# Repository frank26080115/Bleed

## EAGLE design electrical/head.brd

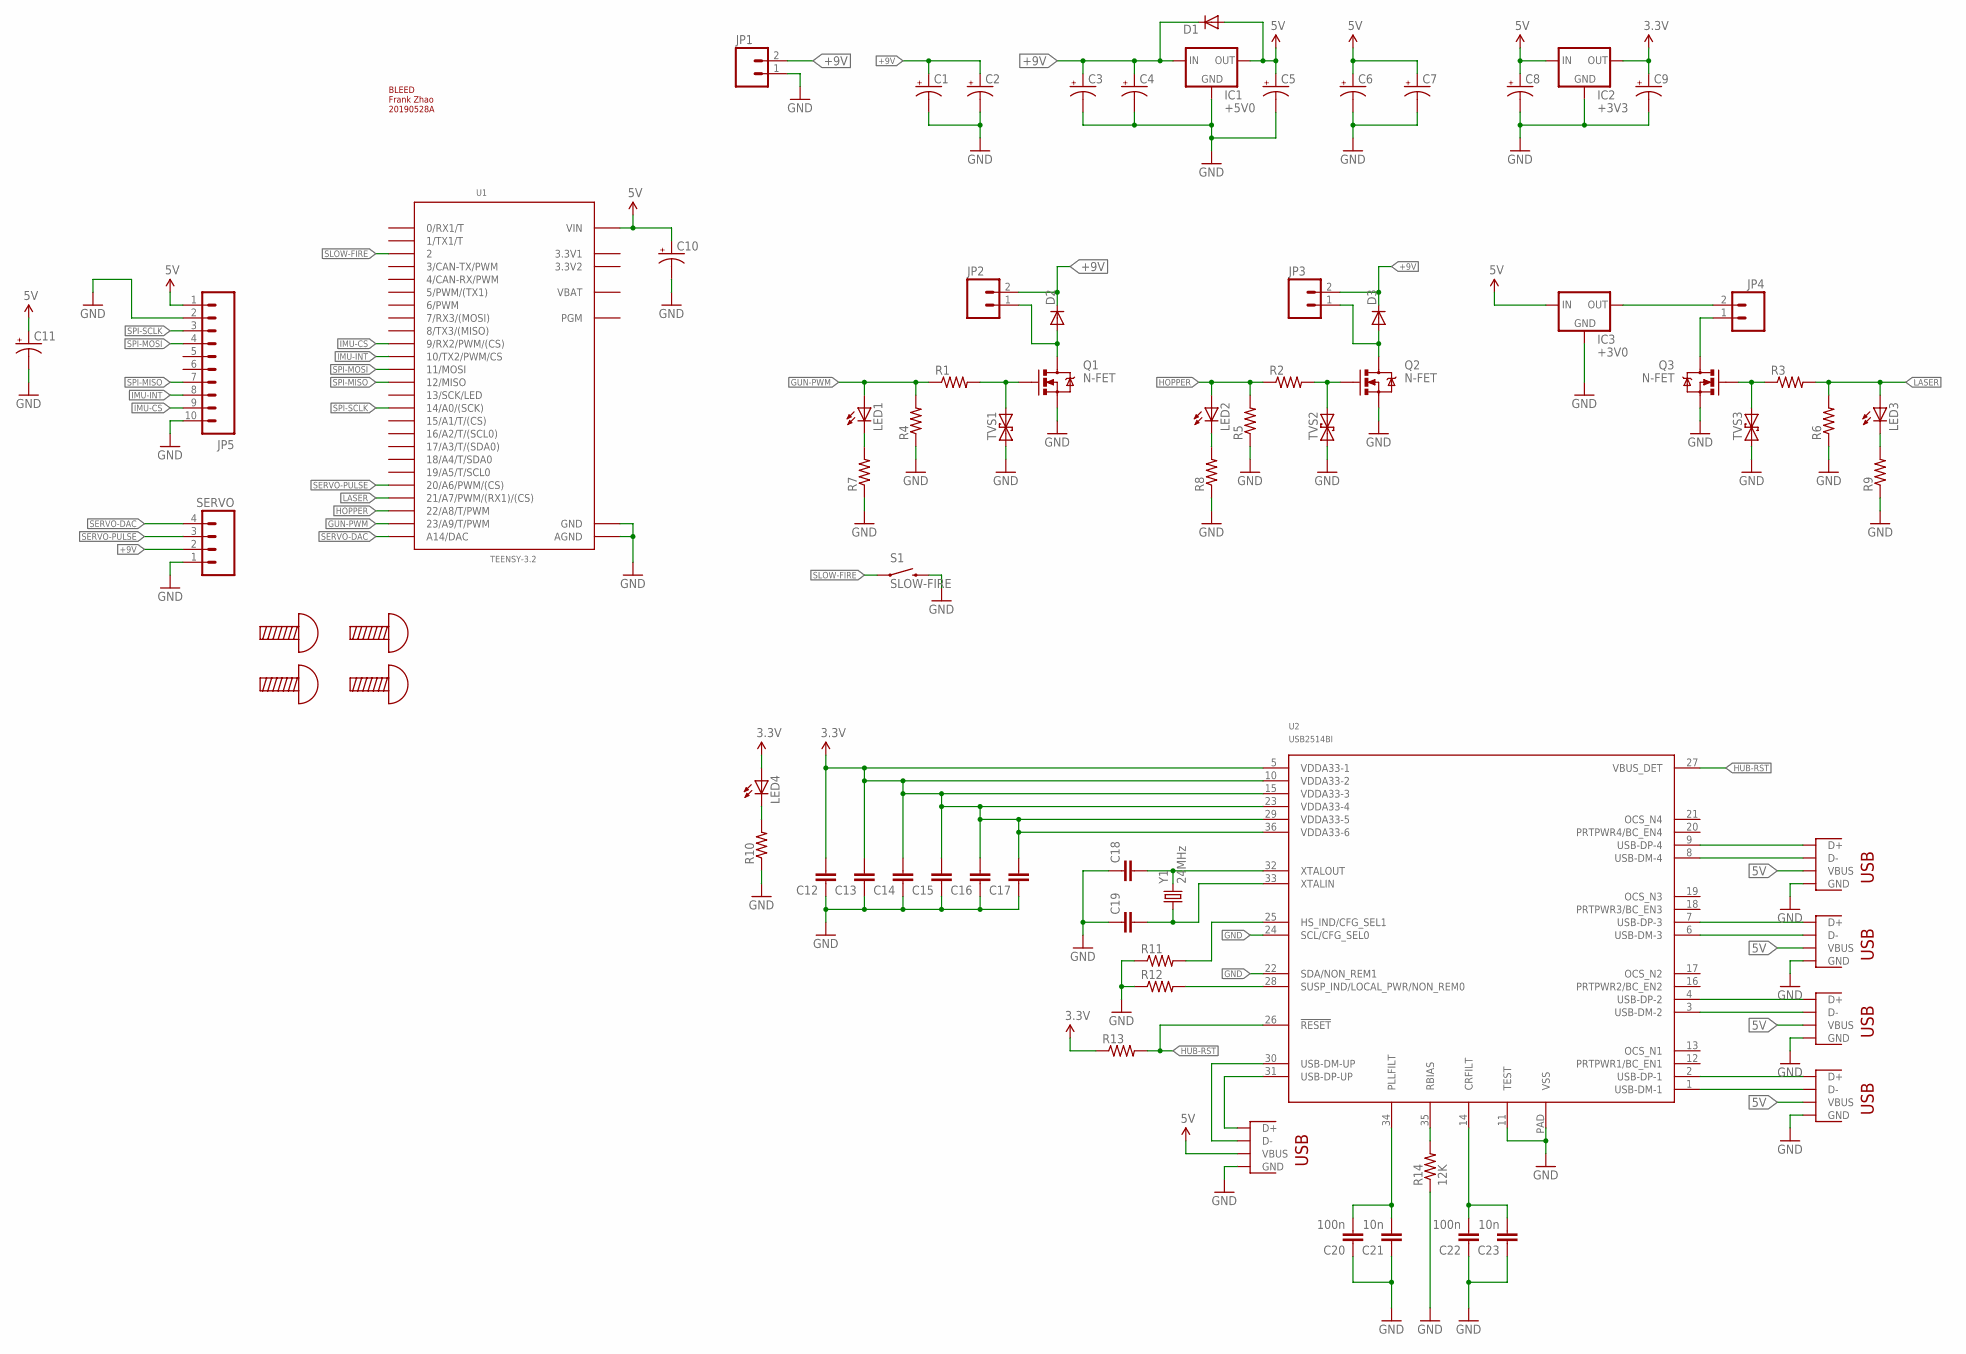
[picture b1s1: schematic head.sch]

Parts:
C1, C2, C3: CAP_POLPTH4; CPOL-RADIAL-1000UF-25V
C4, C5, C6, C7, C8, C9, C10, C11: CAP_POL1206-KIT; EIA3216-KIT
C12, C13, C14, C15, C16, C17, C18, C19: CAP0402-CAP; 0402-CAP
C20, C22: 100n; 0402-CAP
C21, C23: 10n; 0402-CAP
D1, D2, D3: DIODESMA-KIT; SMA-DIODE-KIT
IC1: +5V0; TO220V
IC2: +3V3; SOT23
IC3: +3V0; SOT23
JP1, JP2: M02-TERMBLOCK-3.5MM-OSTTF020161; TERMBLOCK-X2-OSTTF020161
JP3: M02POLAR; MOLEX-1X2
JP4: M02JST-PTH-2; JST-2-PTH
JP5: M10"; 1X10
LED1, LED2, LED3, LED4: LED0603; LED-0603
LOGO1: LOGO_BLEED
Q1, Q2: N-FET; TO220V
Q3: N-FET; SOT23-3
R1, R2, R3, R4, R5, R6, R7, R8, R9: RESISTOR0603-RES; 0603-RES
R10, R11, R12, R13: RESISTOR0402-RES; 0402-RES
R14: 12K; 0402-RES
S1: SLOW-FIRE; TACTILE-SWITCH-1101NE
SCREW1, SCREW2, SCREW3, SCREW4: SCREW-M3
SERVO: M04POLAR; MOLEX-1X4
TVS1, TVS2, TVS3: TVS-SOD323; SOD-323
U1: TEENSY-3.2; TEENSY_3.0-3.2&LC_OUTER_ROW
U2: USB2514BI; QFN-36
X1, X2, X3, X4, X5: USB-JSTXH-VERT-TH; 1X04-JSTXH-VERT-TH
Y1: 24MHz; CRYSTAL-SMD-5X3

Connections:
3.3V: C9.A (+), C12.2, C13.2, C14.2, C15.2, C16.2, C17.2, IC2.2 (OUT), LED4.A, R13.1, U2.5 (VDDA33-1), U2.10 (VDDA33-2), U2.15 (VDDA33-3), U2.23 (VDDA33-4), U2.29 (VDDA33-5), U2.36 (VDDA33-6)
3.3V1: U1.3.3V1
3.3V2: U1.3.3V2
5V: C5.A (+), C6.A (+), C7.A (+), C8.A (+), C10.A (+), C11.A (+), D1.A, IC1.3 (OUT), IC2.3 (IN), IC3.3 (IN), JP5.1, U1.VIN, X1.1 (VBUS), X2.1 (VBUS), X3.1 (VBUS), X4.1 (VBUS), X5.1 (VBUS)
+9V: C1.1 (+), C2.1 (+), C3.1 (+), C4.A (+), D1.C, D2.C, D3.C, IC1.1 (IN), JP1.2, JP2.2, JP3.2, SERVO.2
GND: C1.2 (-), C2.2 (-), C3.2 (-), C4.C (-), C5.C (-), C6.C (-), C7.C (-), C8.C (-), C9.C (-), C10.C (-), C11.C (-), C12.1, C13.1, C14.1, C15.1, C16.1, C17.1, C18.1, C19.1, C20.1, C21.1, C22.1, C23.1, IC1.2 (GND), IC2.1 (GND), IC3.1 (GND), JP1.1, JP5.2, JP5.10, Q1.3 (S), Q2.3 (S), Q3.2 (S), R4.1, R5.1, R6.1, R7.1, R8.1, R9.1, R10.1, R11.1, R12.1, R14.1, S1.2, SERVO.1, TVS1.1, TVS2.1, TVS3.1, U1.AGND, U1.GND, U1.GND1 (GND), U2.11 (TEST), U2.22 (SDA/NON_REM1), U2.24 (SCL/CFG_SEL0), U2.PAD (VSS), X1.4 (GND), X2.4 (GND), X3.4 (GND), X4.4 (GND), X5.4 (GND)
GUN-PWM: LED1.A, R1.1, R4.2, U1.23/A9 (23/A9/T/PWM)
HOPPER: LED2.A, R2.1, R5.2, U1.22/A8 (22/A8/T/PWM)
HUB-RST: R13.2, U2.26 (!RESET), U2.27 (VBUS_DET)
IMU-CS: JP5.9, U1.9 (9/RX2/PWM/(CS))
IMU-INT: JP5.8, U1.10 (10/TX2/PWM/CS)
LASER: LED3.A, R3.2, R6.2, U1.21/A7 (21/A7/PWM/(RX1)/(CS))
unnamed: C18.2, U2.32 (XTALOUT), Y1.3 (2)
unnamed: D2.A, JP2.1, Q1.2 (D)
unnamed: LED4.C, R10.2
unnamed: Q1.1 (G), R1.2, TVS1.2
unnamed: C19.2, U2.33 (XTALIN), Y1.1
unnamed: C20.2, C21.2, U2.34 (PLLFILT)
unnamed: D3.A, JP3.1, Q2.2 (D)
unnamed: Q2.1 (G), R2.2, TVS2.2
unnamed: JP4.1, Q3.3 (D)
unnamed: IC3.2 (OUT), JP4.2
unnamed: LED1.C, R7.2
unnamed: Q3.1 (G), R3.1, TVS3.2
unnamed: LED2.C, R8.2
unnamed: C22.2, C23.2, U2.14 (CRFILT)
unnamed: LED3.C, R9.2
unnamed: R14.2, U2.35 (RBIAS)
unnamed: R11.2, U2.25 (HS_IND/CFG_SEL1)
unnamed: R12.2, U2.28 (SUSP_IND/LOCAL_PWR/NON_REM0)
SERVO-DAC: SERVO.4, U1.RESET/DAC (A14/DAC)
SERVO-PULSE: SERVO.3, U1.20/A6 (20/A6/PWM/(CS))
SLOW-FIRE: S1.1, U1.2
SPI-MISO: JP5.7, U1.12 (12/MISO)
SPI-MOSI: JP5.4, U1.11 (11/MOSI)
SPI-SCLK: JP5.3, U1.14/A0 (14/A0/(SCK))
USB_DOWN1_D_N: U2.1 (USB-DM-1), X4.3 (D-)
USB_DOWN1_D_P: U2.2 (USB-DP-1), X4.2 (D+)
USB_DOWN2_D_N: U2.3 (USB-DM-2), X3.3 (D-)
USB_DOWN2_D_P: U2.4 (USB-DP-2), X3.2 (D+)
USB_DOWN3_D_N: U2.6 (USB-DM-3), X2.3 (D-)
USB_DOWN3_D_P: U2.7 (USB-DP-3), X2.2 (D+)
USB_DOWN4_D_N: U2.8 (USB-DM-4), X1.3 (D-)
USB_DOWN4_D_P: U2.9 (USB-DP-4), X1.2 (D+)
USB_UP_D_N: U2.31 (USB-DP-UP), X5.2 (D+)
USB_UP_D_P: U2.30 (USB-DM-UP), X5.3 (D-)
VBAT: U1.VBAT

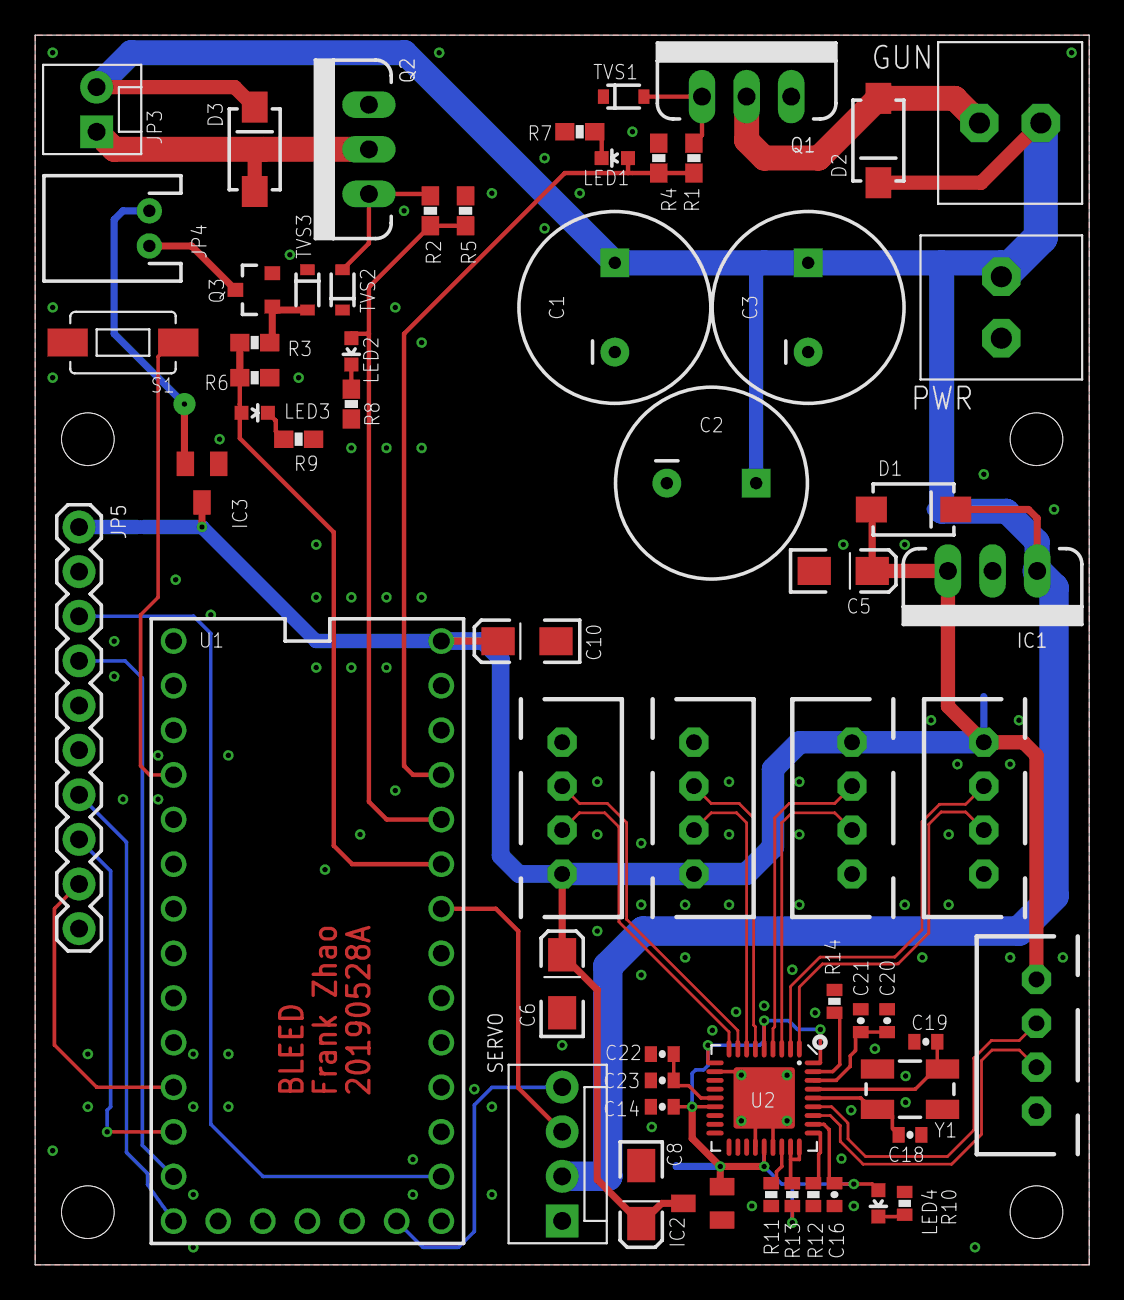
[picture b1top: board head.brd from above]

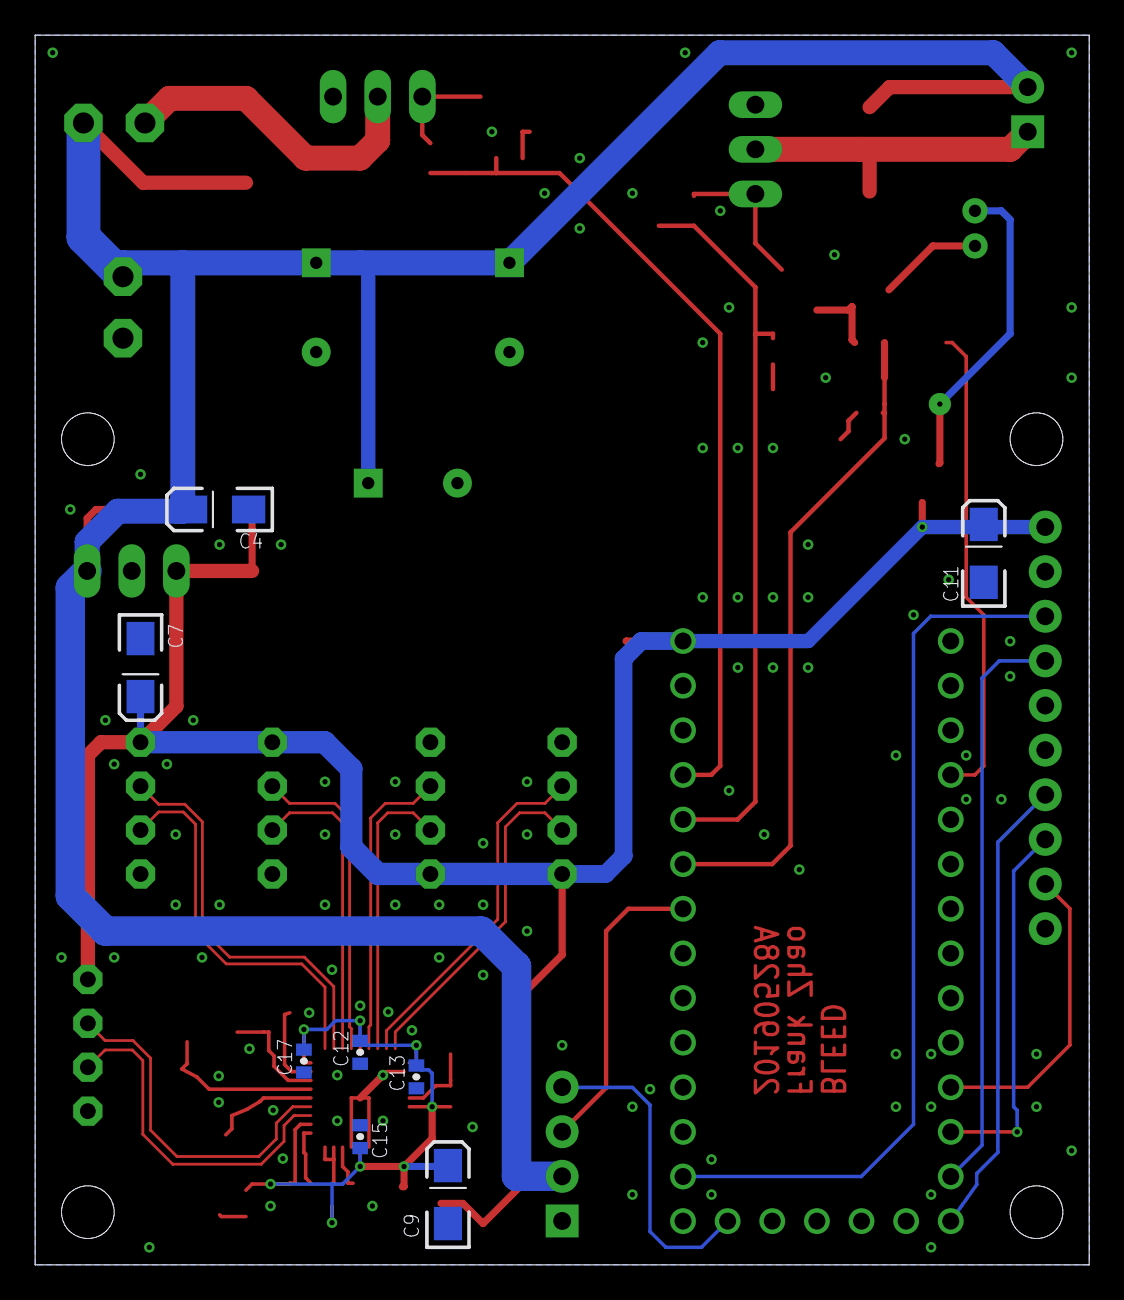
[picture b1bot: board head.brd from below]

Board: 2 copper layers, 60.0 x 70.0 mm, 73 parts (8 on the bottom side), 44 nets.

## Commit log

2019-04-25 added MPU library
2019-04-25 added servo model
2019-04-25 added another servo cad model
2019-04-25 generated command constants for lobot bus servo
2019-04-25 added PXX library
2019-04-25 added SBUS library
2019-04-26 added command line library
2019-05-06 MPU6500: added DMA to SPI implementation of DMP
2019-05-06 started to write LobotServo library
2019-05-06 some mech design progress
2019-05-07 added async statemachine to DMP library
2019-05-07 head tilt code started
2019-05-07 integration of PWMServo library
2019-05-27 circuit progress
2019-05-27 added stance queue WIP
2019-05-28 head circuit WIP
